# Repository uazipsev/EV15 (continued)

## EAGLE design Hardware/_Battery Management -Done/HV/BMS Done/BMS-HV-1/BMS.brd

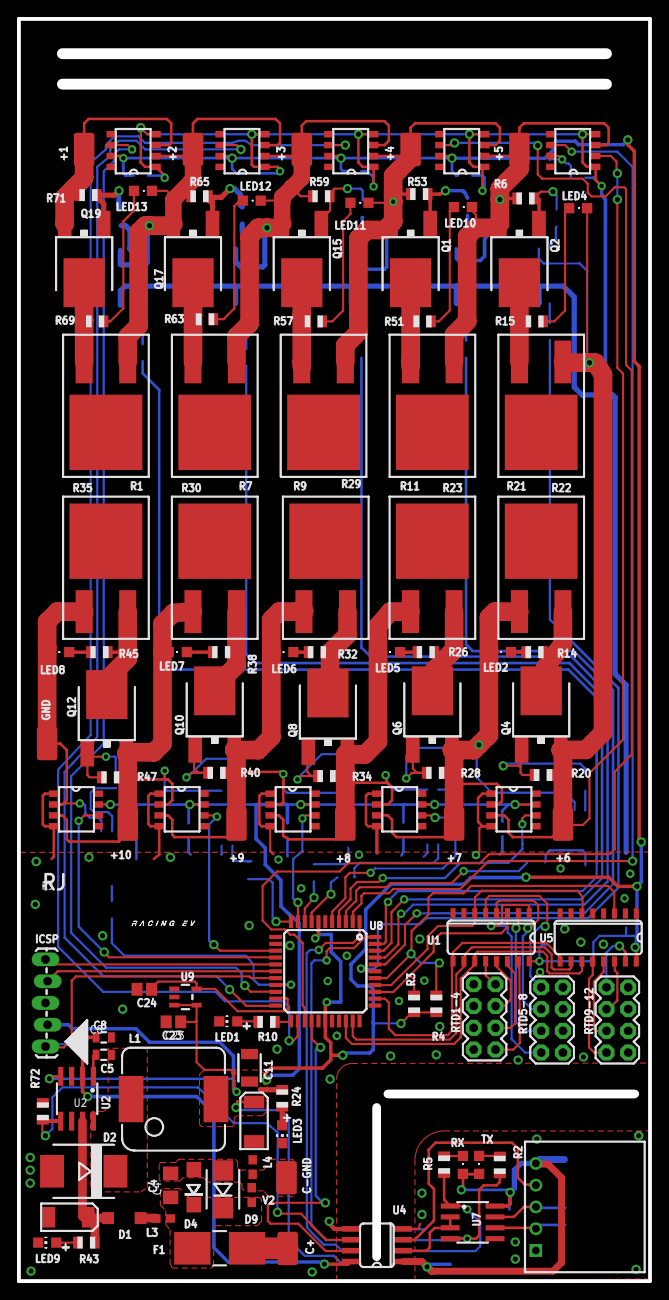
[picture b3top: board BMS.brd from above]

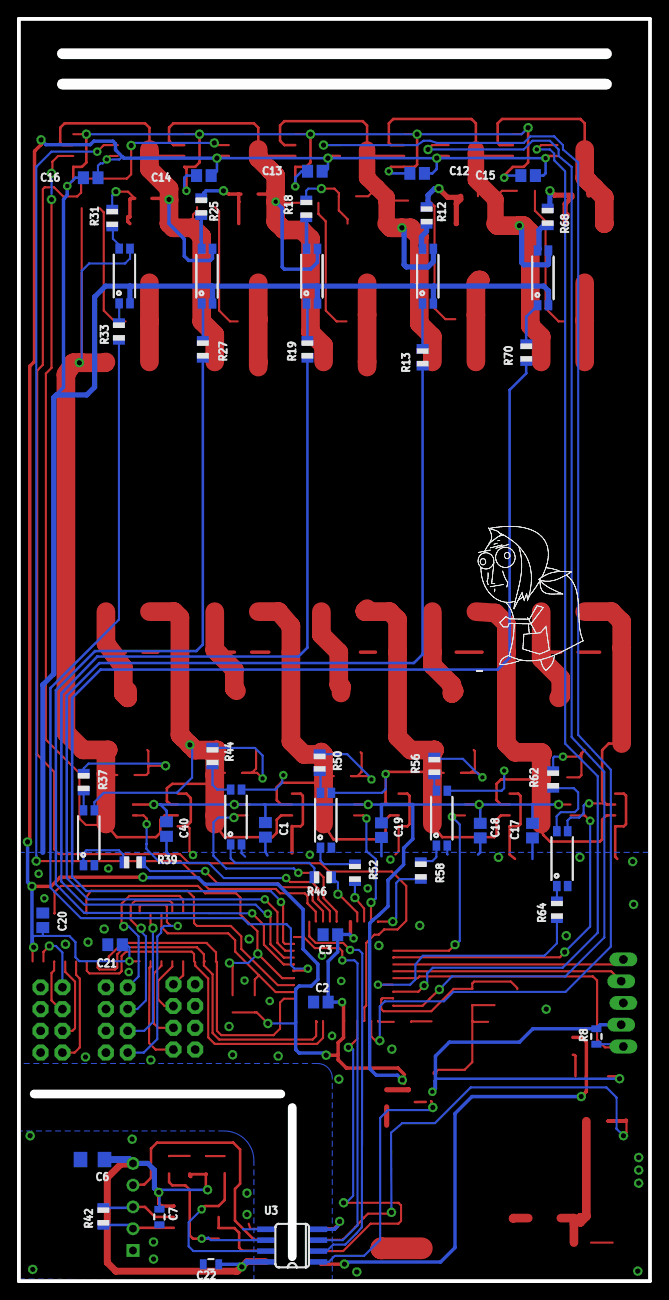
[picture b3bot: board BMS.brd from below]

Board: 2 copper layers, 73.7 x 147.3 mm, 168 parts (51 on the bottom side), 131 nets.

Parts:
+1, +2, +3, +4, +5, +6, +7, +8, +9, +10: M01SMD; LUXEON-PAD
C1, C2, C3, C12, C13, C14, C15, C16, C17, C18, C19, C20, C21, C23, C24, C40: .1uF; C0805
C4: 1uF; 1206
C5, C8: 0.1uF; 0805
C6: 10uF; 1206
C7, C22: .1uF; 0805
C9, C10: 68uF; EIA6032
C11: 1uF; 1210
C+: M01SMD; LUXEON-PAD
C-GND: M01SMD; LUXEON-PAD
D1: 1N4001; SOD123
D2: VS-30BQ060TRPBF; SMC
D4: TVS; DO-214AC
D9: 45V; SMB-DIODE
F1: 01541.25DR; 0154XXDR
GND: M01SMD; LUXEON-PAD
ICSP: 1X05_LOCK_LONGPADS
L1: 7447714101; INDUCTOR_5X3
L3, L4: FERITEBEAD; 0603
LED1, LED3, LED9: CHIP-LED0805
LED2, LED4, LED5, LED6, LED7, LED8, LED10, LED11, LED12, LED13: CHIPLED_0805
Q1, Q2, Q4, Q6, Q8, Q10, Q12, Q15, Q17, Q19: MJD127T4; DPAK
R1, R7, R9, R11, R21, R22, R23, R29, R30, R35: PFC10-5RF1
R2, R5, R10, R24: 1k; R0805
R3, R4, R6, R20, R28, R34, R40, R47, R53, R59, R65, R71, R72: 10k; R0805
R8: 10k; 0805
R12, R18, R25, R31, R37, R44, R50, R56, R62, R68: 330; R0805
R13, R19, R27, R33, R39, R46, R52, R58, R64, R70: 200; R0805
R14, R15, R26, R32, R38, R45, R51, R57, R63, R69: 399; R0805
R42: 120; R0805
R43: 3.3k; R0805
RTD1-4, RTD5-8, RTD9-12: M04X2; 2X4
RX: CHIPLED_0805
TX: CHIPLED_0805
U1, U5: SN74LV4051ADR; SO-16
U2: MAX5035; SO-8
U3, U4: ISO7221ADR; SOIC-8
U6: M5; 5-103635-4
U7: SN75HVD08DR; SO-8
U8: PIC18F45K22; TQFP-44
U9: LM4128CMF-2.0/NOPB; SOT23-5
U$1, U$2, U$3, U$4, U$5, U$6, U$7, U$8, U$9, U$55: LT1990
U$10, U$11, U$12, U$13, U$14, U$15, U$16, U$17, U$18, U$19: TCMT1103-OPTO; SSOP-4
U$20: INDPK1; PICKIT-PIN-1
U$21: OLD_LADYM; 0L-M
U$22: LOGO; L-MS
V2: 45Vdc; 0603

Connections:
+4.1V: C8.1, U2.2, U4.8
+5V: C1.1, C2.1, C3.1, C9.P$1, C11.1, C12.1, C13.1, C14.1, C15.1, C16.1, C17.1, C18.1, C19.1, C20.1, C21.1, C23.1, C40.1, ICSP.2, L1.2, R3.1, R4.1, R8.2, R24.2, U1.16, U2.4, U3.1, U5.16, U8.7, U8.28, U9.3, U9.4, U$1.7, U$2.7, U$3.7, U$4.7, U$5.7, U$6.7, U$7.7, U$8.7, U$9.7, U$55.7
A: U1.11, U5.11, U8.31
B: U1.10, U5.10, U8.32
B1: R70.1, U8.43
B2: R13.1, U8.42
B3: R19.1, U8.41
B4: R27.1, U8.40
B5: R33.1, U8.39
B6: R39.1, U8.3
B7: R46.1, U8.8
B8: R52.1, U8.9
B9: R58.1, U8.11
B10: R64.1, U8.19
C: U1.9, U5.9, U8.35
C1: U8.20, U$9.6
C2: U8.22, U$8.6
C3: U8.24, U$7.6
C4: U8.25, U$6.6
C5: U8.2, U$55.6
C6: U8.4, U$1.6
C7: U8.5, U$2.6
C8: U8.10, U$3.6
C9: U8.14, U$4.6
C10: U8.15, U$5.6
DIR: U4.2, U7.2, U7.3
EN: U4.3, U6.4
GHT: D1.A, L3.2
GND: C1.2, C2.2, C3.2, C8.2, C9.P$2, C10.P$2, C11.2, C12.2, C13.2, C14.2, C15.2, C16.2, C17.2, C18.2, C19.2, C20.2, C21.2, C23.2, C24.2, C40.2, D2.A, ICSP.3, L4.2, LED1.C, LED3.C, LED9.C, R72.1, RTD1-4.2, RTD1-4.4, RTD1-4.6, RTD1-4.8, RTD5-8.1, RTD5-8.3, RTD5-8.5, RTD5-8.7, RTD9-12.2, RTD9-12.4, RTD9-12.6, RTD9-12.8, U1.7, U1.8, U2.3, U2.6, U3.4, U4.5, U5.7, U5.8, U8.6, U8.29, U9.2, U$1.1, U$1.4, U$2.1, U$2.4, U$3.1, U$3.4, U$4.1, U$4.4, U$5.1, U$5.4, U$6.1, U$6.4, U$7.1, U$7.4, U$8.1, U$8.4, U$9.1, U$9.4, U$10.2, U$11.2, U$12.2, U$13.2, U$14.2, U$15.2, U$16.2, U$17.2, U$18.2, U$19.2, U$55.1, U$55.4
GNDIO: C6.2, C7.2, C22.2, U3.5, U4.4, U6.1, U7.5
INH: U1.6, U5.6, U8.37
MODE: U4.7, U8.26
unnamed: LED1.A, R10.1
unnamed: R10.2, U8.23
unnamed: C10.P$1, D1.C, R43.2, U2.7
unnamed: RTD1-4.1, U1.15
unnamed: RTD1-4.3, U1.14
unnamed: C4.1, D4.C, D9.C, F1.2, L3.1, V2.2
unnamed: RTD1-4.5, U1.13
unnamed: R72.2, U2.5, U4.6
unnamed: +6.P$1, LED4.C, Q4.3, R20.1, R22.1, U$1.3, U$14.3, U$55.2
unnamed: RTD1-4.7, U1.12
unnamed: RTD9-12.1, U5.15
unnamed: R2.1, TX.C
unnamed: R5.1, RX.C
unnamed: RTD9-12.3, U5.14
unnamed: LED9.A, R43.1
unnamed: +9.P$1, LED6.C, Q10.3, R9.1, R40.1, U$3.2, U$4.3, U$17.3
unnamed: Q2.1, R6.2, R31.1
unnamed: +10.P$1, LED7.C, Q12.3, R7.1, R47.1, U$4.2, U$5.3, U$18.3
unnamed: RTD9-12.5, U5.13
unnamed: R70.2, U$10.1
unnamed: RTD9-12.7, U5.12
unnamed: R13.2, U$11.1
unnamed: Q4.1, R20.2, R37.1
unnamed: LED4.A, R15.1
unnamed: LED3.A, R24.1
unnamed: C5.2, D2.C, L1.1, U2.8
unnamed: R68.2, U$10.4
unnamed: LED2.A, R14.1
unnamed: R19.2, U$12.1
unnamed: Q4.2, R14.2, R21.2
unnamed: +8.P$1, LED5.C, Q8.3, R11.1, R34.1, U$2.2, U$3.3, U$16.3
unnamed: +7.P$1, LED2.C, Q6.3, R21.1, R28.1, U$1.2, U$2.3, U$15.3
unnamed: Q6.1, R28.2, R44.1
unnamed: R44.2, U$16.4
unnamed: LED5.A, R26.1
unnamed: R27.2, U$13.1
unnamed: Q6.2, R11.2, R26.2
unnamed: C5.1, U2.1
unnamed: C24.1, U8.21, U9.5
unnamed: ICSP.4, U8.17
unnamed: Q8.1, R34.2, R50.1
unnamed: R37.2, U$15.4
unnamed: ICSP.5, U8.16
unnamed: LED6.A, R32.1
unnamed: R33.2, U$14.1
unnamed: ICSP.1, R8.1, U8.18
unnamed: Q8.2, R9.2, R32.2
unnamed: RTD5-8.2, U1.1
unnamed: RTD5-8.4, U1.2
unnamed: Q10.1, R40.2, R56.1
unnamed: R62.2, U$19.4
unnamed: LED7.A, R38.1
unnamed: R39.2, U$15.1
unnamed: Q10.2, R7.2, R38.2
unnamed: RTD5-8.6, U1.4
unnamed: RTD5-8.8, U1.5
unnamed: Q12.1, R47.2, R62.1
unnamed: R12.2, U$11.4
unnamed: LED8.A, R45.1
unnamed: R46.2, U$16.1
unnamed: Q12.2, R1.2, R45.2
unnamed: Q1.1, R25.1, R53.2
unnamed: R18.2, U$12.4
unnamed: Q2.2, R15.2, R22.2
unnamed: R52.2, U$17.1
unnamed: LED10.A, R51.1
unnamed: R25.2, U$13.4
unnamed: Q1.2, R23.2, R51.2
unnamed: +4.P$1, LED11.C, Q1.3, R29.1, R53.1, U$6.3, U$7.2, U$12.3
unnamed: +5.P$1, LED10.C, Q2.3, R6.1, R23.1, U$6.2, U$13.3, U$55.3
unnamed: Q15.1, R18.1, R59.2
unnamed: R58.2, U$18.1
unnamed: LED11.A, R57.1
unnamed: R31.2, U$14.4
unnamed: Q15.2, R29.2, R57.2
unnamed: R64.2, U$19.1
unnamed: R50.2, U$17.4
unnamed: +3.P$1, LED12.C, Q15.3, R30.1, R59.1, U$7.3, U$8.2, U$11.3
unnamed: Q17.1, R12.1, R65.2
unnamed: R56.2, U$18.4
unnamed: LED12.A, R63.1
unnamed: +1.P$1, Q19.3, R71.1, U$9.3
unnamed: Q17.2, R30.2, R63.2
unnamed: +2.P$1, LED13.C, Q17.3, R35.1, R65.1, U$8.3, U$9.2, U$10.3
unnamed: Q19.1, R68.1, R71.2
unnamed: GND.P$1, LED8.C, R1.1, U$5.2, U$19.3
unnamed: LED13.A, R69.1
unnamed: Q19.2, R35.2, R69.2
RS-A: R42.1, U6.2, U7.6
RS-B: R42.2, U6.3, U7.7
RX: R5.2, U3.7, U7.1
RX1: U3.2, U8.1
T1: R3.2, U1.3, U8.36
T2: R4.2, U5.3, U8.38
TX: R2.2, U3.6, U7.4
TX1: U3.3, U8.44
V+: C6.1, C7.1, C22.1, RX.A, TX.A, U3.8, U4.1, U6.5, U7.8
VCC: C+.P$1, F1.1
VSS: C4.2, C-GND.P$1, D4.A, D9.A, L4.1, V2.1

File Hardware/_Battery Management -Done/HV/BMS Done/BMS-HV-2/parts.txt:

Partlist							
							
Exported	from	BMS.sch	at	4/27/2015	11:44:22	AM	
							
EAGLE	Version	6.5.0	Copyright	(c)	1988-2013	CadSoft	
							
Assembly	variant:						
							
Part	Value	Device	Package	Library	Sheet		
							
							
R13	200	R-US_R0805	R0805	adafruit	1		
R19	200	R-US_R0805	R0805	adafruit	1		
R27	200	R-US_R0805	R0805	adafruit	1		
R33	200	R-US_R0805	R0805	adafruit	1		
R39	200	R-US_R0805	R0805	adafruit	1		
R46	200	R-US_R0805	R0805	adafruit	1		
R52	200	R-US_R0805	R0805	adafruit	1		
R58	200	R-US_R0805	R0805	adafruit	1		
R64	200	R-US_R0805	R0805	adafruit	1		
R70	200	R-US_R0805	R0805	adafruit	1		
R12	330	R-US_R0805	R0805	adafruit	1		
R18	330	R-US_R0805	R0805	adafruit	1		
R25	330	R-US_R0805	R0805	adafruit	1		
R31	330	R-US_R0805	R0805	adafruit	1		
R37	330	R-US_R0805	R0805	adafruit	1		
R44	330	R-US_R0805	R0805	adafruit	1		
R50	330	R-US_R0805	R0805	adafruit	1		
R56	330	R-US_R0805	R0805	adafruit	1		
R62	330	R-US_R0805	R0805	adafruit	1		
R68	330	R-US_R0805	R0805	adafruit	1		
R14	399	R-US_R0805	R0805	adafruit	1		
R15	399	R-US_R0805	R0805	adafruit	1		
R26	399	R-US_R0805	R0805	adafruit	1		
R32	399	R-US_R0805	R0805	adafruit	1		
R38	399	R-US_R0805	R0805	adafruit	1		
R45	399	R-US_R0805	R0805	adafruit	1		
R51	399	R-US_R0805	R0805	adafruit	1		
R57	399	R-US_R0805	R0805	adafruit	1		
R63	399	R-US_R0805	R0805	adafruit	1		
R69	399	R-US_R0805	R0805	adafruit	1		
L1	7447714101	INDUCTOR	INDUCTOR_5X3	NASA_LIB	1		
C1	.1uF	C-USC0805	C0805	adafruit	1		
C12	.1uF	C-USC0805	C0805	adafruit	1		
C13	.1uF	C-USC0805	C0805	adafruit	1		
C14	.1uF	C-USC0805	C0805	adafruit	1		
C15	.1uF	C-USC0805	C0805	adafruit	1		
C16	.1uF	C-USC0805	C0805	adafruit	1		
C17	.1uF	C-USC0805	C0805	adafruit	1		
C18	.1uF	C-USC0805	C0805	adafruit	1		
C19	.1uF	C-USC0805	C0805	adafruit	1		
C2	.1uF	C-USC0805	C0805	adafruit	1		
C20	.1uF	C-USC0805	C0805	adafruit	1		
C21	.1uF	C-USC0805	C0805	adafruit	1		
C22	.1uF	CAP0805	805	SparkFun-Passives	1		
C23	.1uF	C-USC0805	C0805	adafruit	1		
C24	.1uF	C-USC0805	C0805	adafruit	1		
C3	.1uF	C-USC0805	C0805	adafruit	1		
C40	.1uF	C-USC0805	C0805	adafruit	1		
C7	.1uF	CAP0805	805	SparkFun-Passives	1		
C5	0.1uF	CAP0805	805	SparkFun-Passives	1		
C8	0.1uF	CAP0805	805	SparkFun-Passives	1		
F1	01541.25DR	0154XXDR	0154XXDR	FSAE	1		
R20	10k	R-US_R0805	R0805	adafruit	1		
R28	10k	R-US_R0805	R0805	adafruit	1		
R3	10k	R-US_R0805	R0805	adafruit	1		
R34	10k	R-US_R0805	R0805	adafruit	1		
R4	10k	R-US_R0805	R0805	adafruit	1		
R40	10k	R-US_R0805	R0805	adafruit	1		
R47	10k	R-US_R0805	R0805	adafruit	1		
R53	10k	R-US_R0805	R0805	adafruit	1		
R59	10k	R-US_R0805	R0805	adafruit	1		
R6	10k	R-US_R0805	R0805	adafruit	1		
R65	10k	R-US_R0805	R0805	adafruit	1		
R71	10k	R-US_R0805	R0805	adafruit	1		
R72	10k	R-US_R0805	R0805	adafruit	1		
R8	10k	RESISTOR0805-RES	805	SparkFun-Passives	1		
C6	10uF	CAP1206	1206	SparkFun-Passives	1		
R10	1k	R-US_R0805	R0805	adafruit	1		
R2	1k	R-US_R0805	R0805	adafruit	1		
R24	1k	R-US_R0805	R0805	adafruit	1		
R5	1k	R-US_R0805	R0805	adafruit	1		
D1	1N4001	DIODE-SOD123	SOD123	diode	1		
C11	1uF	CAP1210	1210	SparkFun-Capacitors	1		
C4	1uF	CAP1206	1206	SparkFun-Capacitors	1		
R43	3.3k	R-US_R0805	R0805	adafruit	1		
D9	45V	DIODE-ZENERSMB	SMB-DIODE	SparkFun	1		
V2	45Vdc	VAR-RES	603	EmEndev	1		
C10	68uF	CAP_POL6032	EIA6032	SparkFun-Passives	1		
C9	68uF	CAP_POL6032	EIA6032	SparkFun-Passives	1		
L3	FERITEBEAD	FERITEBEAD	603	EmEndev	1		
L4	FERITEBEAD	FERITEBEAD	603	EmEndev	1		
U3	ISO7221ADR	ISO7221ADR	SOIC-8	Gasbarre	1		
U4	ISO7221ADR	ISO7221ADR	SOIC-8	Gasbarre	1		
LED10	LEDCHIPLED_0805	LEDCHIPLED_0805	CHIPLED_0805	adafruit	1		
LED11	LEDCHIPLED_0805	LEDCHIPLED_0805	CHIPLED_0805	adafruit	1		
LED12	LEDCHIPLED_0805	LEDCHIPLED_0805	CHIPLED_0805	adafruit	1		
LED13	LEDCHIPLED_0805	LEDCHIPLED_0805	CHIPLED_0805	adafruit	1		
LED2	LEDCHIPLED_0805	LEDCHIPLED_0805	CHIPLED_0805	adafruit	1		
LED4	LEDCHIPLED_0805	LEDCHIPLED_0805	CHIPLED_0805	adafruit	1		
LED5	LEDCHIPLED_0805	LEDCHIPLED_0805	CHIPLED_0805	adafruit	1		
LED6	LEDCHIPLED_0805	LEDCHIPLED_0805	CHIPLED_0805	adafruit	1		
LED7	LEDCHIPLED_0805	LEDCHIPLED_0805	CHIPLED_0805	adafruit	1		
LED8	LEDCHIPLED_0805	LEDCHIPLED_0805	CHIPLED_0805	adafruit	1		
LED1	LEDCHIP-LED0805	LEDCHIP-LED0805	CHIP-LED0805	adafruit	1		
LED3	LEDCHIP-LED0805	LEDCHIP-LED0805	CHIP-LED0805	adafruit	1		
LED9	LEDCHIP-LED0805	LEDCHIP-LED0805	CHIP-LED0805	adafruit	1		
U9	LM4128CMF-2.0/NOPB	LM4128-2.5VREF	SOT23-5	SparkFun-PowerIC	1		
							
							
RTD1-4	M04X2	M04X2	2X4	SparkFun-Connectors	1		
RTD5-8	M04X2	M04X2	2X4	SparkFun-Connectors	1		
RTD9-12	M04X2	M04X2	2X4	SparkFun-Connectors	1		
							
U6	M5	M5	5-103635-4	FSAE	1		
U2	MAX5035	MAX5035	SO-8	FSAE	1		
Q1	MJD127T4	MJD127T4	DPAK	FSAE	1		http://www.digikey.com/product-search/en?pv7=2&pv1291=87&k=M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
Q10	MJD127T4	MJD127T4	DPAK	FSAE	1		
Q12	MJD127T4	MJD127T4	DPAK	FSAE	1		
Q15	MJD127T4	MJD127T4	DPAK	FSAE	1		
Q17	MJD127T4	MJD127T4	DPAK	FSAE	1		
Q19	MJD127T4	MJD127T4	DPAK	FSAE	1		
Q2	MJD127T4	MJD127T4	DPAK	FSAE	1		
Q4	MJD127T4	MJD127T4	DPAK	FSAE	1		
Q6	MJD127T4	MJD127T4	DPAK	FSAE	1		
Q8	MJD127T4	MJD127T4	DPAK	FSAE	1		
R1	PFC10-5RF1	PFC10-5RF1	PFC10-5RF1	FSAE	1		http://www.digikey.com/product-detail/en/PFC10-5RF1/696-1422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
R11	PFC10-5RF1	PFC10-5RF1	PFC10-5RF1	FSAE	1		
R21	PFC10-5RF1	PFC10-5RF1	PFC10-5RF1	FSAE	1		
R22	PFC10-5RF1	PFC10-5RF1	PFC10-5RF1	FSAE	1		
R23	PFC10-5RF1	PFC10-5RF1	PFC10-5RF1	FSAE	1		
R29	PFC10-5RF1	PFC10-5RF1	PFC10-5RF1	FSAE	1		
R30	PFC10-5RF1	PFC10-5RF1	PFC10-5RF1	FSAE	1		
R35	PFC10-5RF1	PFC10-5RF1	PFC10-5RF1	FSAE	1		
R7	PFC10-5RF1	PFC10-5RF1	PFC10-5RF1	FSAE	1		
R9	PFC10-5RF1	PFC10-5RF1	PFC10-5RF1	FSAE	1		
							
U1	SN74LV4051ADR	SN74LV4051ADR	SO-16	FSAE	1		
U5	SN74LV4051ADR	SN74LV4051ADR	SO-16	FSAE	1		
U7	SN75HVD08DR	SN75HVD08DR	SO-8	FSAE	1		
U$10	TCMT1103-OPTO	TCMT1103-OPTO	SSOP-4	SparkFun-DiscreteSemi	1		http://www.digikey.com/product-detail/en/TCMT1103/TCMT1103CT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
U$11	TCMT1103-OPTO	TCMT1103-OPTO	SSOP-4	SparkFun-DiscreteSemi	1		
U$12	TCMT1103-OPTO	TCMT1103-OPTO	SSOP-4	SparkFun-DiscreteSemi	1		
U$13	TCMT1103-OPTO	TCMT1103-OPTO	SSOP-4	SparkFun-DiscreteSemi	1		
U$14	TCMT1103-OPTO	TCMT1103-OPTO	SSOP-4	SparkFun-DiscreteSemi	1		
U$15	TCMT1103-OPTO	TCMT1103-OPTO	SSOP-4	SparkFun-DiscreteSemi	1		
U$16	TCMT1103-OPTO	TCMT1103-OPTO	SSOP-4	SparkFun-DiscreteSemi	1		
U$17	TCMT1103-OPTO	TCMT1103-OPTO	SSOP-4	SparkFun-DiscreteSemi	1		
U$18	TCMT1103-OPTO	TCMT1103-OPTO	SSOP-4	SparkFun-DiscreteSemi	1		
U$19	TCMT1103-OPTO	TCMT1103-OPTO	SSOP-4	SparkFun-DiscreteSemi	1		
D4	TVS	TVS	DO-214AC	NASA_LIB	1		
D2	VS-30BQ060TRPBF	DIODESMC/DO-214AB	SMC	SparkFun-DiscreteSemi	1		
RX		LEDCHIPLED_0805	CHIPLED_0805	adafruit	1		
TX		LEDCHIPLED_0805	CHIPLED_0805	adafruit	1

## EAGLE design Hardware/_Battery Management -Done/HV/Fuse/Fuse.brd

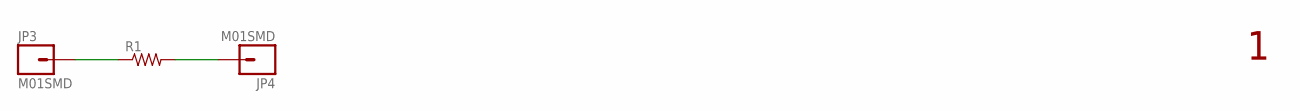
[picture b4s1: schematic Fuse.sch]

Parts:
JP3, JP4: M01SMD; LUXEON-PAD
R1: RESISTOR1206; 1206

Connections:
unnamed: JP3.P$1, R1.1
unnamed: JP4.P$1, R1.2

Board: 2 copper layers, 3 parts (2 on the bottom side), 2 nets, no tracks yet.

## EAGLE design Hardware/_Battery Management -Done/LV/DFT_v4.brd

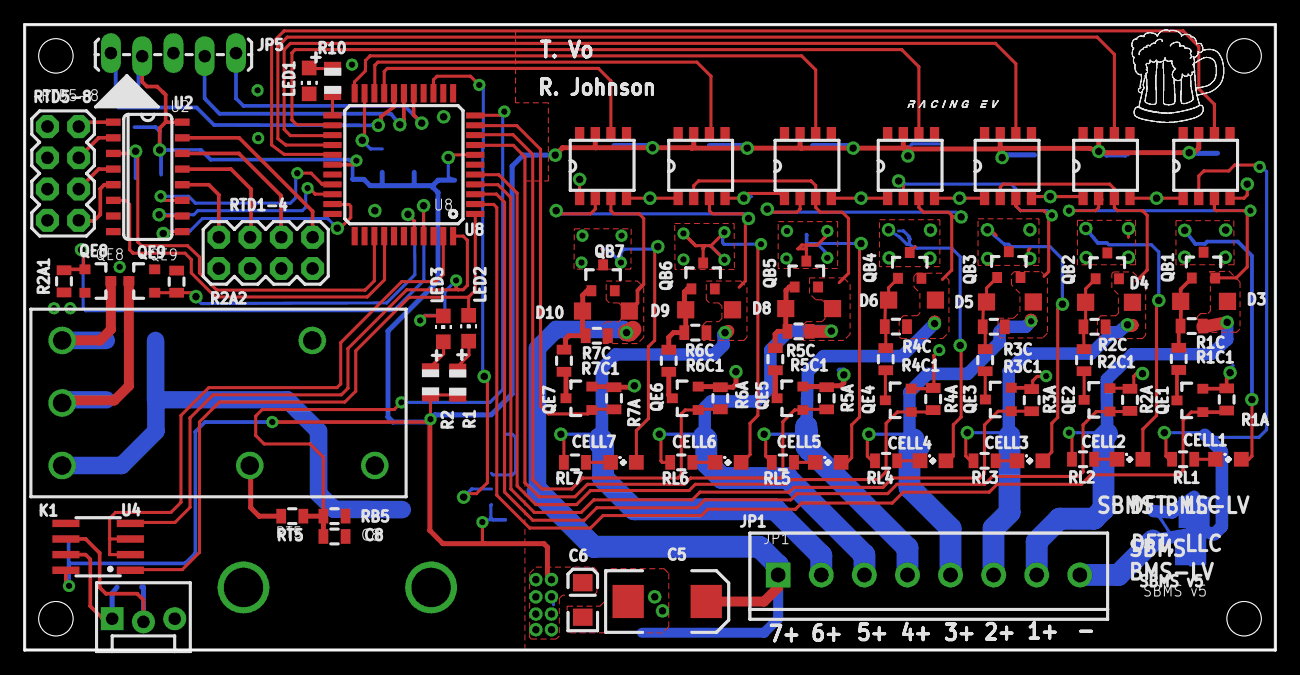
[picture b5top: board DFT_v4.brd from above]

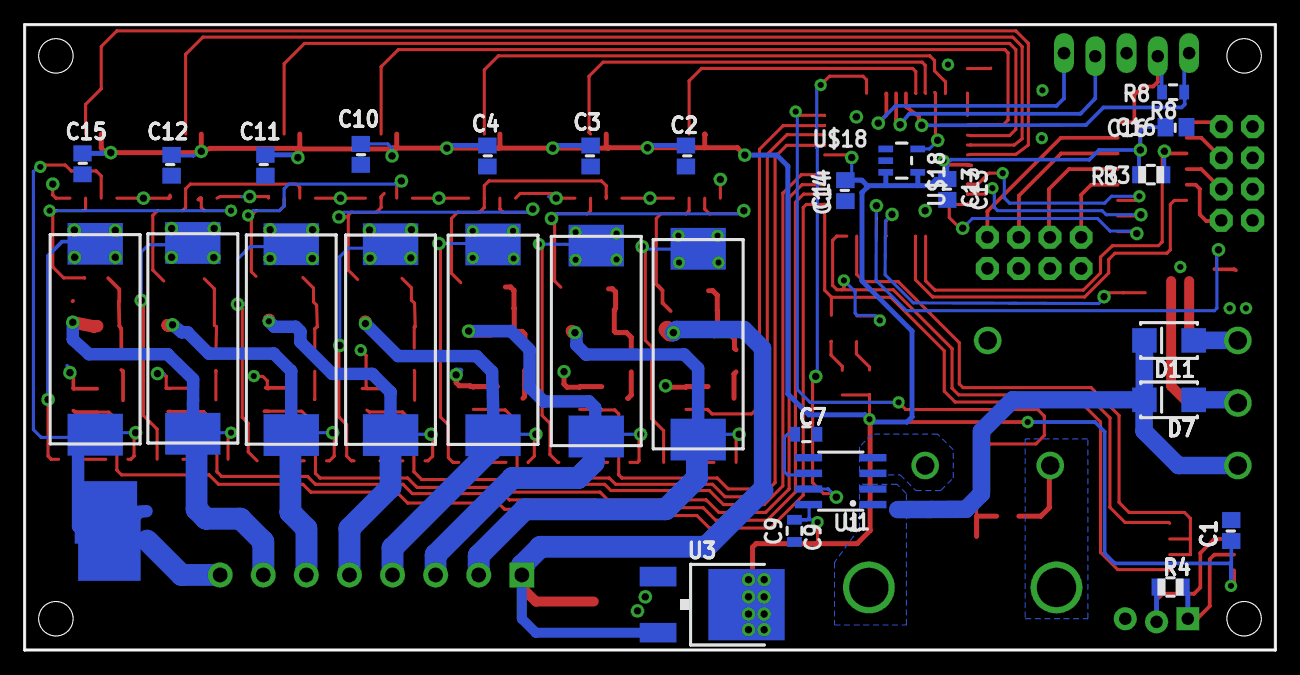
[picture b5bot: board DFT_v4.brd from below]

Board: 2 copper layers, 101.6 x 50.8 mm, 120 parts (30 on the bottom side), 88 nets.

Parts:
C1, C2, C3, C4, C10, C11, C12, C13, C14, C15, C16: .1uF; C0805
C5: 22uF; EIA7343
C6: 10uF; EIA3216
C7, C8: 0.1uF; 0805
C9: 0.1u; 0805
CELL1, CELL2, CELL3, CELL4, CELL5, CELL6, CELL7: LED; SML0805
D3, D4, D5, D6, D8, D9, D10: SOD123
D7, D11: SMA-DIODE_ALT
JP1: 0532580829; SCREWTERMINAL-3.5MM-8
JP2: MOLEX-1X3_LOCK
JP5: 1X05_LOCK_LONGPADS
K1: ADJ14024
LED1, LED2, LED3: CHIP-LED0805
QB1, QB2, QB3, QB4, QB5, QB6, QB7: DMP2305U; SOT-23
QE1, QE2, QE3, QE4, QE5, QE6, QE7, QE8, QE9: BSS123; SOT-23
R1, R2, R10: 1k; R0805
R1A, R1C, R2A, R2A1, R2A2, R2C, R3A, R3C, R4A, R4C, R5A, R5C, R6A, R6C, R7A, R7C: 22k; 0805
R1C1: 1k; 0805
R2C1, R3C1, R4C1, R5C1, R6C1, R7C1: 2k; 0805
R3: 10k; R0805
R4: 120; R0805
R8: 10k; 0805
RB5: 5.36k; 0805
RL1, RL2, RL3, RL4, RL5, RL6, RL7: 200; 0805
RT5: 32.4k; 0805
RTD1-4, RTD5-8: M04X2; 2X4
U1: ACS712; SO-8
U2: SN74LV4051ADR; SO-16
U3: IFX27001TF V50; V-REG_DPACK
U4: SN75HVD08DR; SO-8
U8: PIC18F45K22; TQFP-44
U$1, U$2, U$3, U$4, U$8, U$9, U$10: SHUNT; SM-5
U$5, U$7: VIRTUALGROUND; VIRTUALSHORT
U$6: B-S
U$11, U$12, U$13, U$14, U$15, U$16, U$17: LT1990
U$18: LM4128CMF-2.0/NOPB; SOT23-5
U$19: INDPK1; PICKIT-PIN-1
U$20: LOGO; L-MS

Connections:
+5V: C1.1, C2.1, C3.1, C4.1, C6.A, C9.1, C10.1, C11.1, C12.1, C13.1, C14.1, C15.1, C16.1, JP5.2, R1.2, R2.2, R3.1, R8.2, U1.8, U2.16, U3.4, U4.8, U8.7, U8.28, U$11.7, U$12.7, U$13.7, U$14.7, U$15.7, U$16.7, U$17.7, U$18.3, U$18.4
A: U2.11, U8.30
AN_CELL1: U8.27, U$11.6
AN_CELL2: U8.26, U$12.6
AN_CELL3: U8.25, U$13.6
AN_CELL4: U8.24, U$14.6
AN_CELL5: U8.22, U$15.6
AN_CELL6: U8.20, U$16.6
AN_CELL7: U8.19, U$17.6
ASEN: U1.7, U8.14
B: U2.10, U8.31
BATTPACK+: D7.C, D11.C, K1.C+, U1.1, U1.2
BP_ENBL1: QE1.1, R1A.1, U8.2
BP_ENBL2: QE2.1, R2A.1, U8.3
BP_ENBL3: QE3.1, R3A.1, U8.4
BP_ENBL4: QE4.1, R4A.1, U8.5
BP_ENBL5: QE5.1, R5A.1, U8.8
BP_ENBL6: QE6.1, R6A.1, U8.9
BP_ENBL7: QE7.1, R7A.1, U8.10
C: U2.9, U8.32
CELL1V+: D3.C, JP1.7, QB1.2, R1C.2, RL2.2, U$2.P$1, U$11.3, U$12.2
CELL1V-: JP1.8, RL1.2, U$1.P$1, U$5.P$1, U$7.P$2, U$11.2
CELL2V+: D4.C, JP1.6, QB2.2, R2C.1, RL3.2, U$3.P$1, U$12.3, U$13.2
CELL3V+: D5.C, JP1.5, QB3.2, R3C.1, RL4.2, U$4.P$1, U$13.3, U$14.2
CELL4V+: D6.C, JP1.4, QB4.2, R4C.1, RL5.2, U$8.P$1, U$14.3, U$15.2
CELL5V+: D8.C, JP1.3, QB5.2, R5C.1, RL6.2, U$9.P$1, U$15.3, U$16.2
CELL6V+: D9.C, JP1.2, QB6.2, R6C.1, RL7.2, U$10.P$1, U$16.3, U$17.2
CELL7V+: C5.A, D10.C, JP1.1, QB7.2, R7C.1, U3.3, U$17.3
GND: C1.2, C2.2, C3.2, C4.2, C5.C, C6.C, C7.2, C8.2, C9.2, C10.2, C11.2, C12.2, C13.2, C14.2, C15.2, C16.2, JP2.3, JP5.3, LED1.C, QE1.2, QE2.2, QE3.2, QE4.2, QE5.2, QE6.2, QE7.2, QE8.2, QE9.2, R1A.2, R2A.2, R2A1.2, R2A2.2, R3A.2, R4A.2, R5A.2, R6A.2, R7A.2, RB5.1, RTD1-4.2, RTD1-4.4, RTD1-4.6, RTD1-4.8, RTD5-8.1, RTD5-8.3, RTD5-8.5, RTD5-8.7, U1.5, U2.7, U2.8, U3.1, U4.5, U8.6, U8.29, U$5.P$2, U$7.P$1, U$11.1, U$11.4, U$12.1, U$12.4, U$13.1, U$13.4, U$14.1, U$14.4, U$15.1, U$15.4, U$16.1, U$16.4, U$17.1, U$17.4, U$18.2
INH: U2.6, U8.37
IN_OUT: K1.NO, RT5.2
unnamed: LED2.A, R1.1
unnamed: LED3.A, R2.1
unnamed: D4.A, QB2.1, R2C.2, R2C1.1
unnamed: D11.A, K1.-8-S, QE8.3
unnamed: JP5.4, U8.17
unnamed: QE1.3, R1C1.1
unnamed: D5.A, QB3.1, R3C.2, R3C1.1
unnamed: D6.A, QB4.1, R4C.2, R4C1.1
unnamed: D3.A, QB1.1, R1C.1, R1C1.2
unnamed: CELL1.A, QB1.3, U$1.P$2
unnamed: K1.C, U1.3, U1.4
unnamed: CELL2.A, QB2.3, U$2.P$2
unnamed: CELL4.A, QB4.3, U$4.P$2
unnamed: D7.A, K1.-9-R, QE9.3
unnamed: CELL1.C, RL1.1
unnamed: QE4.3, R4C1.2
unnamed: CELL3.C, RL3.1
unnamed: R10.2, U8.23
unnamed: CELL3.A, QB3.3, U$3.P$2
unnamed: RTD1-4.1, U2.15
unnamed: C7.1, U1.6
unnamed: RTD1-4.3, U2.14
unnamed: JP2.2, R4.1, U4.6
unnamed: RTD1-4.5, U2.13
unnamed: RTD1-4.7, U2.12
unnamed: CELL2.C, RL2.1
unnamed: JP2.1, R4.2, U4.7
unnamed: CELL4.C, RL4.1
unnamed: QE2.3, R2C1.2
unnamed: QE3.3, R3C1.2
unnamed: JP5.5, U8.16
unnamed: RTD5-8.2, U2.1
unnamed: D8.A, QB5.1, R5C.2, R5C1.1
unnamed: CELL5.A, QB5.3, U$8.P$2
unnamed: CELL5.C, RL5.1
unnamed: QE5.3, R5C1.2
unnamed: D9.A, QB6.1, R6C.2, R6C1.1
unnamed: CELL6.A, QB6.3, U$9.P$2
unnamed: CELL6.C, RL6.1
unnamed: D10.A, QB7.1, R7C.2, R7C1.1
unnamed: QE6.3, R6C1.2
unnamed: CELL7.A, QB7.3, U$10.P$2
unnamed: CELL7.C, RL7.1
unnamed: QE7.3, R7C1.2
unnamed: JP5.1, R8.1, U8.18
unnamed: LED1.A, R10.1
unnamed: RTD5-8.4, U2.2
unnamed: RTD5-8.6, U2.4
unnamed: RTD5-8.8, U2.5
RSET: QE9.1, R2A2.1, U8.40
RX1: LED2.C, U4.1, U8.1
SET: QE8.1, R2A1.1, U8.41
T1: R3.2, U2.3, U8.36
TX1: LED3.C, U4.4, U8.44
U4: U4.2, U4.3, U8.43
VEXTERNAL: C8.1, RB5.2, RT5.1, U8.11
VREF-: U8.21, U$18.5
